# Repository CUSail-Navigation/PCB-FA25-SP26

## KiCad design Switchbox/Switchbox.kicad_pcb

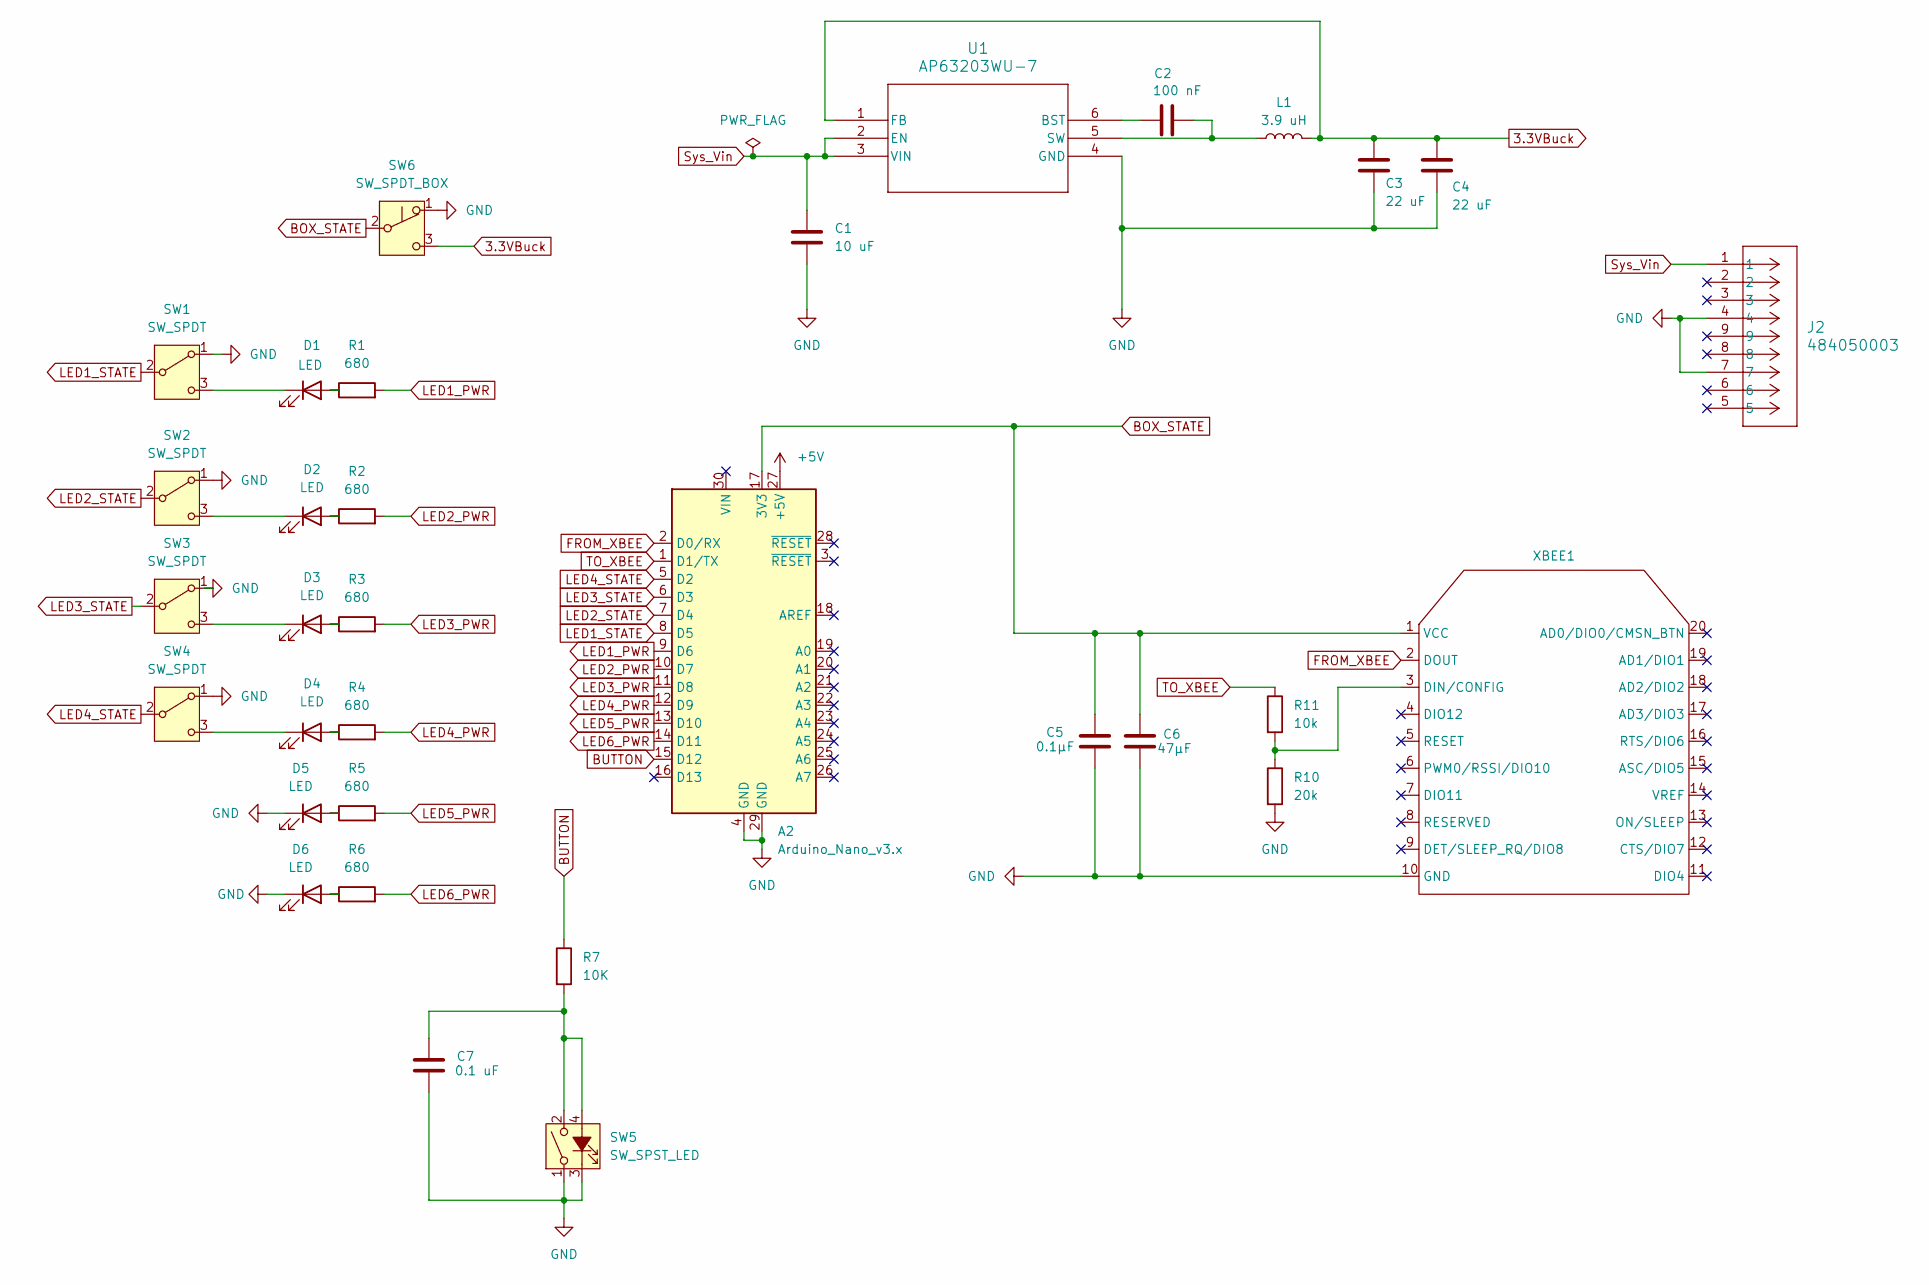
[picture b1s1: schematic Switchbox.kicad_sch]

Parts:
A2: Arduino_Nano_v3.x; Arduino_Nano
C1: 10 uF; CAPC1005X70N
C2: 100 nF; C_0603_1608Metric_Pad1.08x0.95mm_HandSolder
C3, C4: 22 uF; CAPC3216X190N
C5: 0.1µF; CAPC0603X33N
C6: 47µF; CAPC2012X145N
C7: 0.1 uF; CAPC0603X33N
D1, D2, D3, D4, D5, D6: LED; 2_pin_header
J2: 484050003; usba_footprint
L1: 3.9 uH; IND_BOURNS_SRR5018
R1, R2, R3, R4, R5, R6: 680; R_0805_2012Metric_Pad1.20x1.40mm_HandSolder
R7: 10K; R_0805_2012Metric_Pad1.20x1.40mm_HandSolder
R10: 20k; R_0805_2012Metric_Pad1.20x1.40mm_HandSolder
R11: 10k; R_0805_2012Metric_Pad1.20x1.40mm_HandSolder
SW1, SW2, SW3, SW4: SW_SPDT; 3_pin_header
SW5: SW_SPST_LED; 4_pin_header
SW6: SW_SPDT_BOX; 3_pin_header
U1: AP63203WU-7; buck
XBEE1: xbee

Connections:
3.3VBuck: C3.1, C4.1, L1.2, SW6.3 (C), U1.1 (FB)
+5V: A2.27 (+5V)
BOX_STATE: A2.17 (3V3), C5.1, C6.1, SW6.2 (B), XBEE1.1 (VCC)
BUTTON: A2.15 (D12), R7.1
FROM_XBEE: A2.2 (D0/RX), XBEE1.2 (DOUT)
GND: A2.4 (GND), A2.29 (GND), C1.2, C3.2, C4.2, C5.2, C6.2, C7.2, D5.1 (K), D6.1 (K), J2.4, J2.7, R10.2, SW1.1 (A), SW2.1 (A), SW3.1 (A), SW4.1 (A), SW5.1, SW5.3 (K), SW6.1 (A), U1.4 (GND), XBEE1.10 (GND)
LED1_PWR: A2.9 (D6), R1.2
LED1_STATE: A2.8 (D5), SW1.2 (B)
LED2_PWR: A2.10 (D7), R2.2
LED2_STATE: A2.7 (D4), SW2.2 (B)
LED3_PWR: A2.11 (D8), R3.2
LED3_STATE: A2.6 (D3), SW3.2 (B)
LED4_PWR: A2.12 (D9), R4.2
LED4_STATE: A2.5 (D2), SW4.2 (B)
LED5_PWR: A2.13 (D10), R5.2
LED6_PWR: A2.14 (D11), R6.2
unnamed: D1.2 (A), R1.1
unnamed: D1.1 (K), SW1.3 (C)
unnamed: D2.2 (A), R2.1
unnamed: D2.1 (K), SW2.3 (C)
unnamed: D3.2 (A), R3.1
unnamed: D3.1 (K), SW3.3 (C)
unnamed: D4.2 (A), R4.1
unnamed: D4.1 (K), SW4.3 (C)
unnamed: D5.2 (A), R5.1
unnamed: D6.2 (A), R6.1
unnamed: C7.1, R7.2, SW5.2, SW5.4 (A)
unnamed: C2.1, U1.6 (BST)
unnamed: C2.2, L1.1, U1.5 (SW)
unnamed: R10.1, R11.2, XBEE1.3 (DIN/CONFIG)
Sys_Vin: C1.1, J2.1, U1.2 (EN), U1.3 (VIN)
TO_XBEE: A2.1 (D1/TX), R11.1

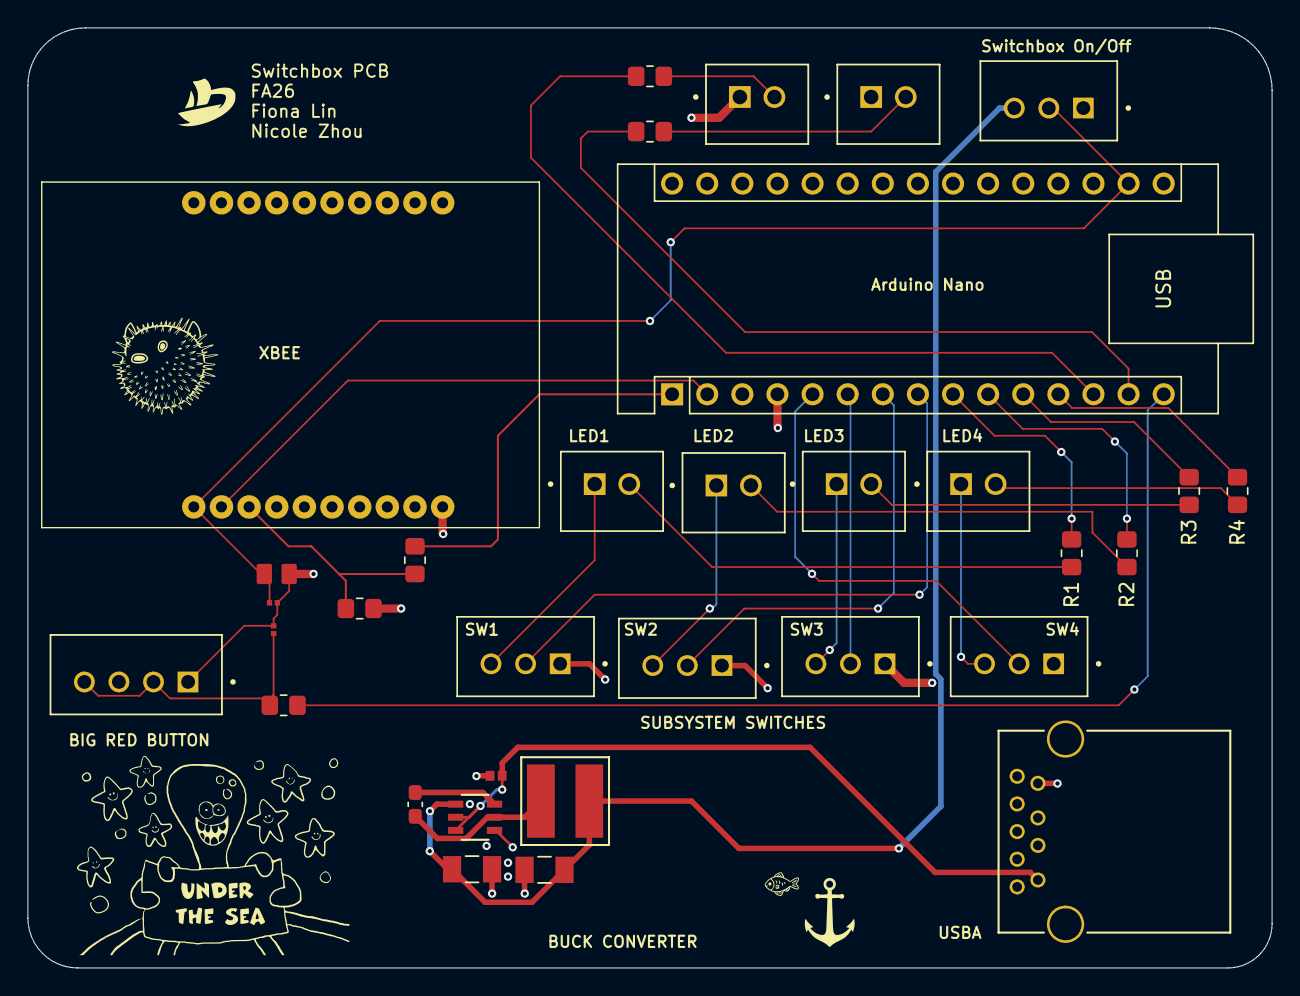
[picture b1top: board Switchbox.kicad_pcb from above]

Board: 4 copper layers, 90.0 x 68.0 mm, 33 parts (0 on the bottom side), 31 nets.

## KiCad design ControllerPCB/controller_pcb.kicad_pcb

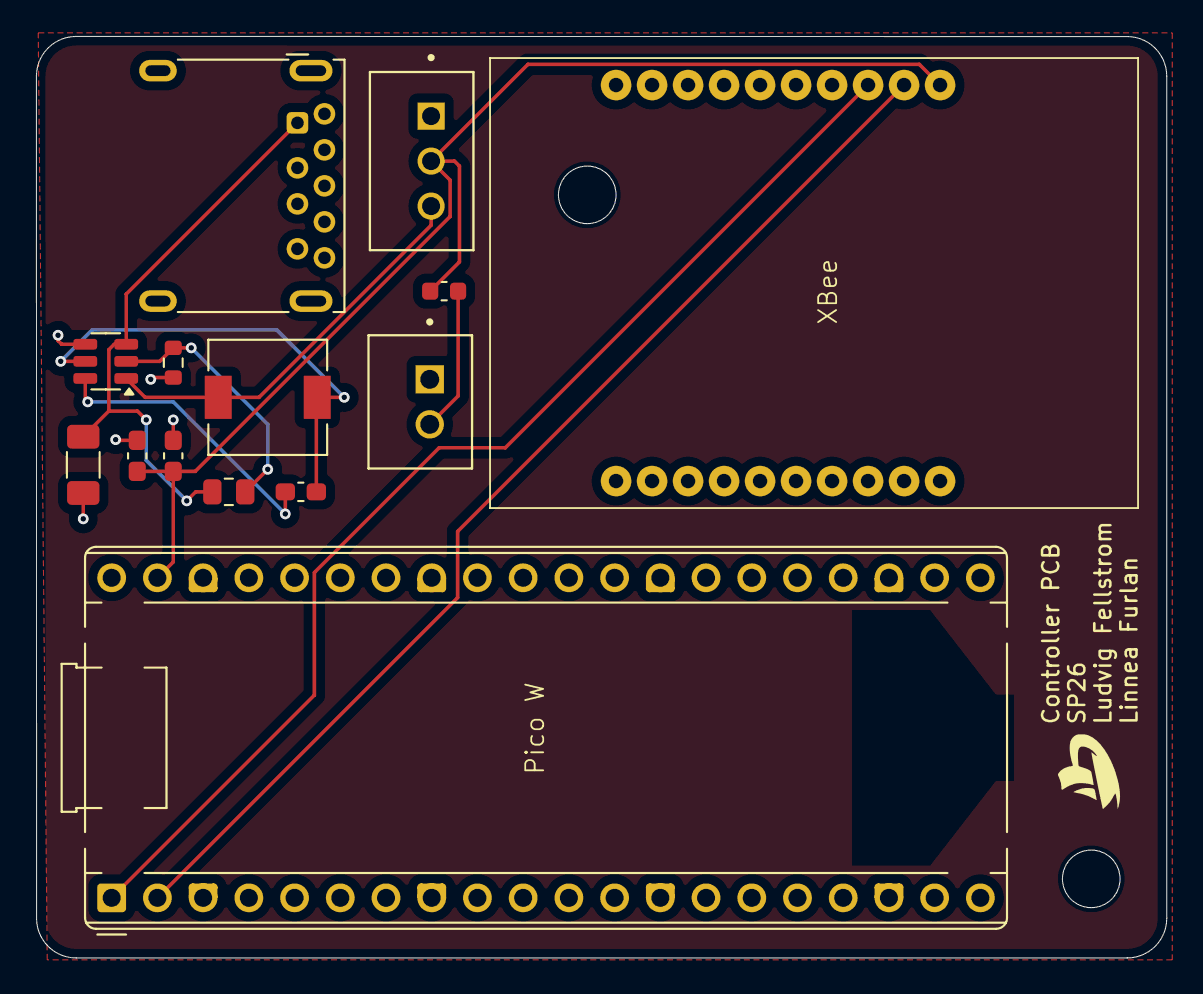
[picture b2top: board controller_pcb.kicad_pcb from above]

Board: 2 copper layers, 62.8 x 51.2 mm, 16 parts (0 on the bottom side), 10 nets.

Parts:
C1: 10µF; C_1206_3216Metric_Pad1.33x1.80mm_HandSolder
C2: 0.1µF; C_0603_1608Metric_Pad1.08x0.95mm_HandSolder
C3, C4: 22µF; C_0603_1608Metric_Pad1.08x0.95mm_HandSolder
D1: LED; 2_pin_header
H1, H2: MountingHole; MountingHole_3.2mm_M3
J1: USB3_A; USB3_A_Molex_48393-001
L1: 4.7µH; L_6.3x6.3_H3
PWR_SW1: SW_SPDT_BOX; 3_pin_header
R1: 100; C_0603_1608Metric
R3: 100k; R_0805_2012Metric
R_Buck_3: 100k; R_0603_1608Metric
U1: Pico; RaspberryPi_Pico_Common_THT
U2: xbee
U3: AP63203WU; TSOT-23-6

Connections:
/DOUT: U1.2 (GPIO1), U2.2 (DOUT)
GND: C1.2, C3.2, C4.2, D1.1 (K), J1.4 (GND), J1.7 (DRAIN), J1.10 (SHIELD), PWR_SW1.1 (A), R_Buck_3.2, U1.3 (GND), U1.8 (GND), U1.13 (GND), U1.18 (GND), U1.23 (GND), U1.28 (GND), U1.38 (GND), U2.10 (GND), U3.4 (GND)
unnamed: D1.2 (A), R1.2
unnamed: C1.1, J1.1 (VBUS), R3.2, U3.3 (IN)
unnamed: C3.1, C4.1, PWR_SW1.2 (B), R1.1, U1.39 (VSYS), U2.1 (VCC)
unnamed: L1.2, PWR_SW1.3 (C), U3.1 (FB)
unnamed: U1.1 (GPIO0), U2.3 (DIN/CONFIG)
unnamed: C2.1, U3.6 (BST)
unnamed: R3.1, R_Buck_3.1, U3.2 (EN)
unnamed: C2.2, L1.1, U3.5 (SW)

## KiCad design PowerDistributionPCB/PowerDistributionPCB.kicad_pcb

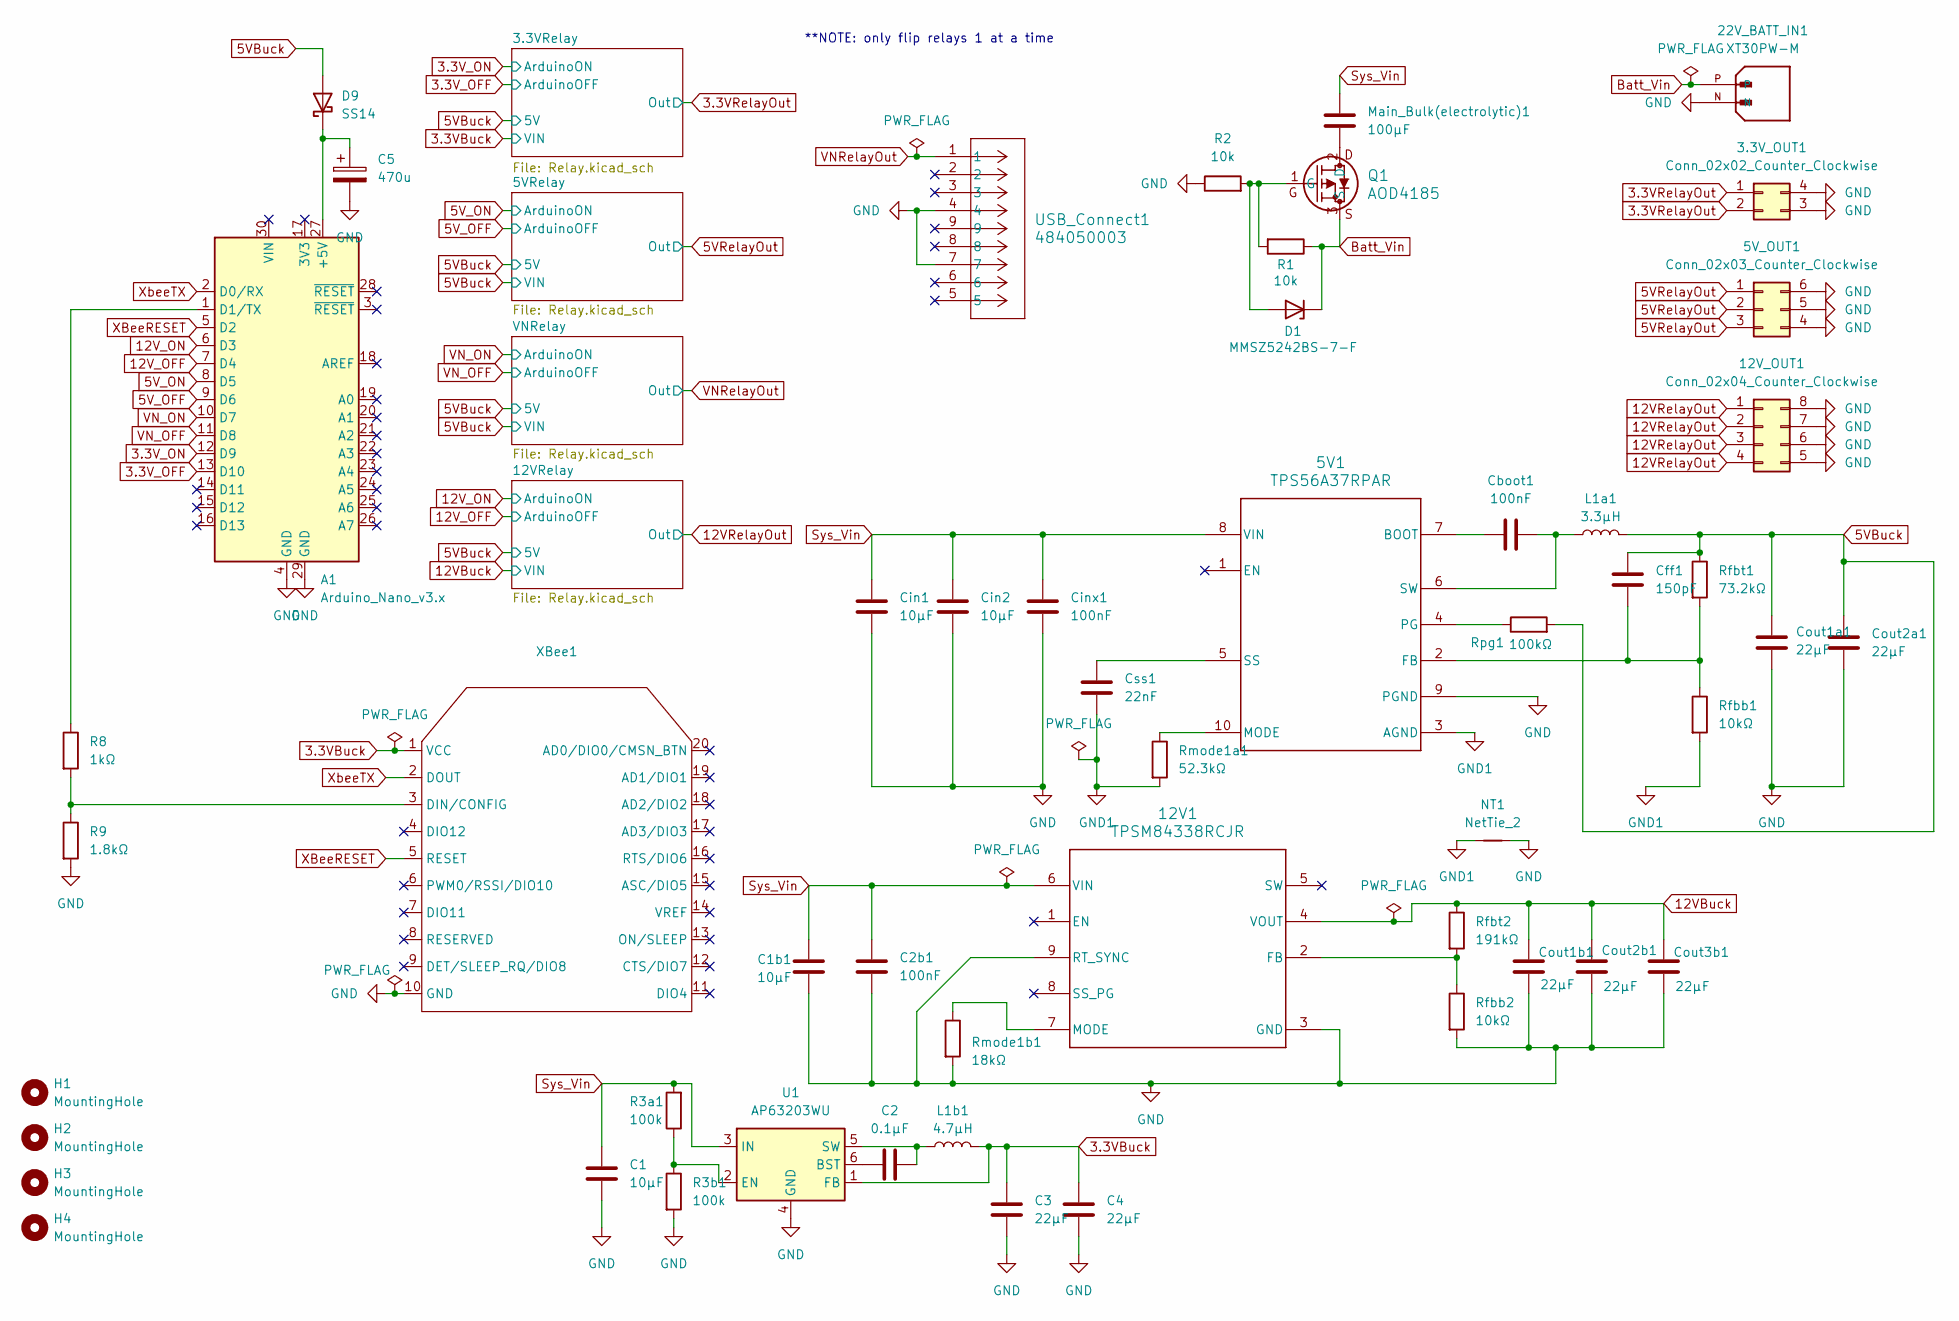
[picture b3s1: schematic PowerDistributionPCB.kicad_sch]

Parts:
3.3V_OUT1: Conn_02x02_Counter_Clockwise; Molex_Mini-Fit_Jr_5566-04A_2x02_P4.20mm_Vertical
5V1: TPS56A37RPAR; RPA0010A-MFG
5V_OUT1: Conn_02x03_Counter_Clockwise; Molex_Mini-Fit_Jr_5566-06A_2x03_P4.20mm_Vertical
12V1: TPSM84338RCJR; buck_correct
12V_OUT1: Conn_02x04_Counter_Clockwise; Molex_Mini-Fit_Jr_5566-08A_2x04_P4.20mm_Vertical
22V_BATT_IN1: XT30PW-M; PARTREV 1.2
A1: Arduino_Nano_v3.x; Arduino_Nano
C1: 10µF; C_1206_3216Metric_Pad1.33x1.80mm_HandSolder
C1b1: 10µF; C_1210_3225Metric_Pad1.33x2.70mm_HandSolder
C2: 0.1µF; C_0603_1608Metric_Pad1.08x0.95mm_HandSolder
C2b1: 100nF; C_0201_0603Metric_Pad0.64x0.40mm_HandSolder
C3, C4: 22µF; C_0603_1608Metric_Pad1.08x0.95mm_HandSolder
C5: 470u; CP_Elec_8x10.5
Cboot1: 100nF; C_0201_0603Metric_Pad0.64x0.40mm_HandSolder
Cff1: 150pF; C_0201_0603Metric_Pad0.64x0.40mm_HandSolder
Cin1, Cin2: 10µF; C_1210_3225Metric_Pad1.33x2.70mm_HandSolder
Cinx1: 100nF; C_0805_2012Metric_Pad1.18x1.45mm_HandSolder
Cout1a1, Cout2a1: 22µF; C_1210_3225Metric_Pad1.33x2.70mm_HandSolder
Cout1b1, Cout2b1, Cout3b1: 22µF; C_1206_3216Metric_Pad1.33x1.80mm_HandSolder
Css1: 22nF; C_0402_1005Metric_Pad0.74x0.62mm_HandSolder
D1: MMSZ5242BS-7-F
D9: SS14; D_SMA
H1, H2, H3, H4: MountingHole; MountingHole_3.2mm_M3
L1a1: 3.3µH; L_Coilcraft_XAL7070-XXX
L1b1: 4.7µH; VLS4012
Main_Bulk(electrolytic)1: 100µF; C_1210_3225Metric_Pad1.33x2.70mm_HandSolder
NT1: NetTie_2; NetTie-2_SMD_Pad0.5mm
Q1: AOD4185
R1, R2: 10k; R_0805_2012Metric_Pad1.20x1.40mm_HandSolder
R3a1, R3b1: 100k; R_0805_2012Metric_Pad1.20x1.40mm_HandSolder
R8: 1kΩ; R_0805_2012Metric_Pad1.20x1.40mm_HandSolder
R9: 1.8kΩ; R_0805_2012Metric_Pad1.20x1.40mm_HandSolder
Rfbb1, Rfbb2: 10kΩ; R_0201_0603Metric_Pad0.64x0.40mm_HandSolder
Rfbt1: 73.2kΩ; R_0805_2012Metric_Pad1.20x1.40mm_HandSolder
Rfbt2: 191kΩ; R_0201_0603Metric_Pad0.64x0.40mm_HandSolder
Rmode1a1: 52.3kΩ; R_0402_1005Metric_Pad0.72x0.64mm_HandSolder
Rmode1b1: 18kΩ; C_0201_0603Metric_Pad0.64x0.40mm_HandSolder
Rpg1: 100kΩ; R_0402_1005Metric_Pad0.72x0.64mm_HandSolder
U1: AP63203WU; TSOT-23-6
USB_Connect1: 484050003; CONN_484050003_MOL
XBee1: XBee

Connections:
3.3VRelayOut: 3.3V_OUT1.1, 3.3V_OUT1.2; also elsewhere on the board
3.3V_OFF: A1.13 (D10); also elsewhere on the board
3.3V_ON: A1.12 (D9); also elsewhere on the board
5VBuck: Cff1.1, Cout1a1.1, Cout2a1.1, D9.2 (A), L1a1.2, Rfbt1.1, Rpg1.2; also elsewhere on the board
5VRelayOut: 5V_OUT1.1, 5V_OUT1.2, 5V_OUT1.3; also elsewhere on the board
5V_OFF: A1.9 (D6); also elsewhere on the board
5V_ON: A1.8 (D5); also elsewhere on the board
12VBuck: 12V1.4 (VOUT), Cout1b1.1, Cout2b1.1, Cout3b1.1, Rfbt2.1; also elsewhere on the board
12VRelayOut: 12V_OUT1.1, 12V_OUT1.2, 12V_OUT1.3, 12V_OUT1.4; also elsewhere on the board
12V_OFF: A1.7 (D4); also elsewhere on the board
12V_ON: A1.6 (D3); also elsewhere on the board
Batt_Vin: 22V_BATT_IN1.P, D1.1 (K), Q1.3 (S), R1.1; also elsewhere on the board
GND: 3.3V_OUT1.3, 3.3V_OUT1.4, 5V1.9 (PGND), 5V_OUT1.4, 5V_OUT1.5, 5V_OUT1.6, 12V1.3 (GND), 12V1.9 (RT_SYNC), 12V_OUT1.5, 12V_OUT1.6, 12V_OUT1.7, 12V_OUT1.8, 22V_BATT_IN1.N, A1.4 (GND), A1.29 (GND), C1.2, C1b1.2, C2b1.2, C3.2, C4.2, C5.2, Cin1.2, Cin2.2, Cinx1.2, Cout1a1.2, Cout1b1.2, Cout2a1.2, Cout2b1.2, Cout3b1.2, NT1.2, R2.1, R3b1.2, R9.2, Rfbb2.2, Rmode1b1.2, U1.4 (GND), USB_Connect1.4, USB_Connect1.7, XBee1.10 (GND); also elsewhere on the board
GND1: 5V1.3 (AGND), Css1.2, NT1.1, Rfbb1.2, Rmode1a1.2
unnamed: 5V1.7 (BOOT), Cboot1.2
unnamed: 5V1.2 (FB), Cff1.2, Rfbb1.1, Rfbt1.2
unnamed: 5V1.10 (MODE), Rmode1a1.1
unnamed: 5V1.4 (PG), Rpg1.1
unnamed: 5V1.5 (SS), Css1.1
unnamed: 5V1.6 (SW), Cboot1.1, L1a1.1
unnamed 20: 12V1.2 (FB), Rfbb2.1, Rfbt2.2; also elsewhere on the board
unnamed 21: 12V1.7 (MODE), Rmode1b1.1; also elsewhere on the board
unnamed: A1.27 (+5V), C5.1, D9.1 (K)
unnamed: A1.1 (D1/TX), R8.1
unnamed: D1.2 (A), Q1.1 (G), R1.2, R2.2
unnamed 37: Main_Bulk(electrolytic)1.2, Q1.2 (D); also elsewhere on the board
unnamed: C2.1, U1.6 (BST)
unnamed: R3a1.1, R3b1.1, U1.2 (EN)
unnamed: C2.2, L1b1.1, U1.5 (SW)
unnamed: R8.2, R9.1, XBee1.3 (DIN/CONFIG)
Sys_Vin: 5V1.8 (VIN), 12V1.6 (VIN), C1.1, C1b1.1, C2b1.1, Cin1.1, Cin2.1, Cinx1.1, Main_Bulk(electrolytic)1.1, R3a1.2, U1.3 (IN); also elsewhere on the board
VNRelayOut: USB_Connect1.1; also elsewhere on the board
VN_OFF: A1.11 (D8); also elsewhere on the board
VN_ON: A1.10 (D7); also elsewhere on the board
XBeeRESET: A1.5 (D2), XBee1.5 (RESET)
XbeeTX: A1.2 (D0/RX), XBee1.2 (DOUT)

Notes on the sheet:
**NOTE: only flip relays 1 at a time

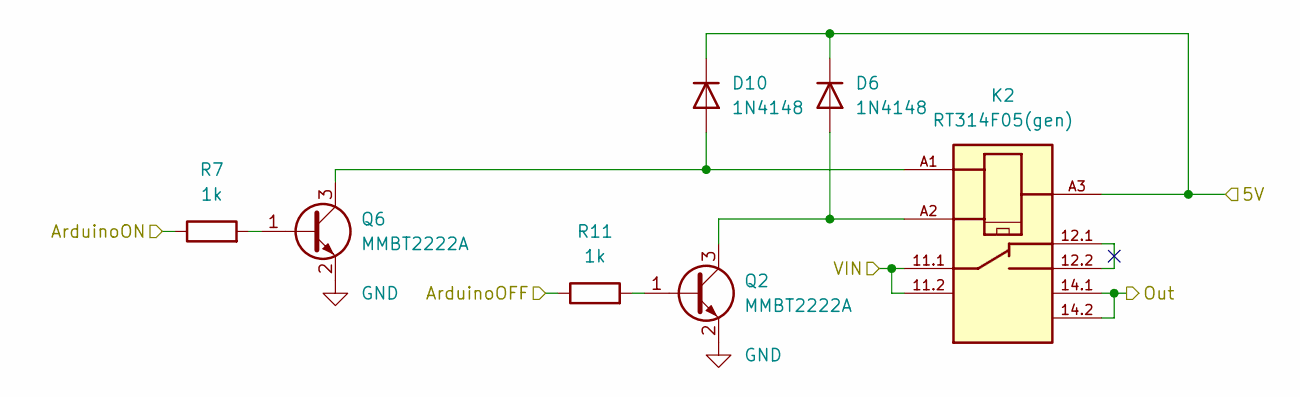
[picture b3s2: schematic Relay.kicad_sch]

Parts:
D6, D10: 1N4148; D_DO-35_SOD27_P7.62mm_Horizontal
K2: RT314F05(gen); RT314F05; VOLTAGE_RATING 5VDC; PART_DESCRIPTION RELAY GEN PURPOSE SPDT 16A 5V
Q2, Q6: MMBT2222A; SOT-23
R7, R11: 1k; R_0805_2012Metric_Pad1.20x1.40mm_HandSolder

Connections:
3.3VRelayOut: K2.14.1, K2.14.2; also elsewhere on the board
3.3V_OFF: R11.1; also elsewhere on the board
3.3V_ON: R7.1; also elsewhere on the board
5VBuck: D6.1 (K), D10.1 (K), K2.A3; also elsewhere on the board
GND: Q2.2 (E), Q6.2 (E); also elsewhere on the board
unnamed: D6.2 (A), K2.A2, Q2.3 (C)
unnamed: D10.2 (A), K2.A1, Q6.3 (C)
unnamed: K2.11.1, K2.11.2
unnamed: Q2.1 (B), R11.2
unnamed: Q6.1 (B), R7.2

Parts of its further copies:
D2, D3, D4, D5, D7, D8: 1N4148; D_DO-35_SOD27_P7.62mm_Horizontal
K1, K3, K4: RT314F05(gen); RT314F05; VOLTAGE_RATING 5VDC; PART_DESCRIPTION RELAY GEN PURPOSE SPDT 16A 5V
Q7, Q8, Q9, Q10, Q11, Q12: MMBT2222A; SOT-23
R3, R4, R5, R6, R15, R16: 1k; R_0805_2012Metric_Pad1.20x1.40mm_HandSolder

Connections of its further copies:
5VBuck: D2.1 (K), D3.1 (K), D4.1 (K), D5.1 (K), D7.1 (K), D8.1 (K), K1.12.1, K1.12.2, K1.A3, K3.12.1, K3.12.2, K3.A3, K4.A3; also elsewhere on the board
5VRelayOut: K1.14.1, K1.14.2; also elsewhere on the board
5V_OFF: R4.1; also elsewhere on the board
5V_ON: R3.1; also elsewhere on the board
12VBuck: K4.12.1, K4.12.2; also elsewhere on the board
12VRelayOut: K4.14.1, K4.14.2; also elsewhere on the board
12V_OFF: R16.1; also elsewhere on the board
12V_ON: R15.1; also elsewhere on the board
GND: Q7.2 (E), Q8.2 (E), Q9.2 (E), Q10.2 (E), Q11.2 (E), Q12.2 (E); also elsewhere on the board
unnamed: D2.2 (A), K1.A1, Q10.3 (C)
unnamed: D3.2 (A), K1.A2, Q11.3 (C)
unnamed: D4.2 (A), K3.A1, Q7.3 (C)
unnamed: D5.2 (A), K3.A2, Q8.3 (C)
unnamed: D7.2 (A), K4.A1, Q9.3 (C)
unnamed: D8.2 (A), K4.A2, Q12.3 (C)
unnamed: K1.11.1, K1.11.2
unnamed: K3.11.1, K3.11.2
unnamed: K4.11.1, K4.11.2
unnamed: Q7.1 (B), R5.2
unnamed: Q8.1 (B), R6.2
unnamed: Q9.1 (B), R15.2
unnamed: Q10.1 (B), R3.2
unnamed: Q11.1 (B), R4.2
unnamed: Q12.1 (B), R16.2
VNRelayOut: K3.14.1, K3.14.2; also elsewhere on the board
VN_OFF: R6.1; also elsewhere on the board
VN_ON: R5.1; also elsewhere on the board

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
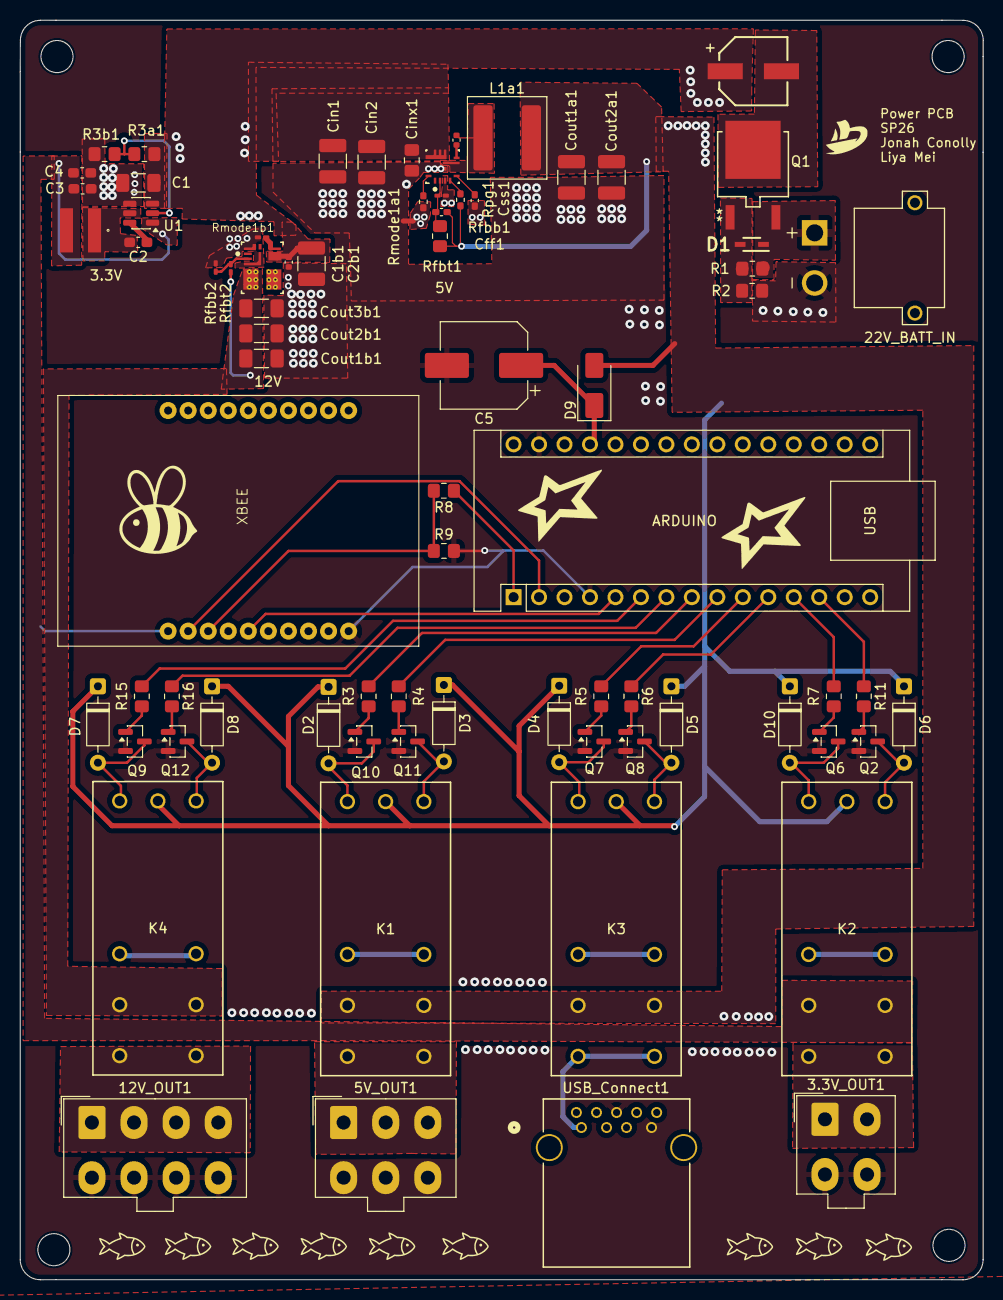
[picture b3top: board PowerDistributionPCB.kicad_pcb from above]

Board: 4 copper layers, 96.0 x 125.6 mm, 80 parts (0 on the bottom side), 57 nets.

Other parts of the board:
12V: TPSM84338RCJR; buck_correct
22V_BATT_IN: XT30PW-M
Main_Bulk: 100µF; WCAP-PSLP_6.3X7.7_DXL_

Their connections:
12VBuck: 12V.4 (VOUT); also elsewhere on the board
Batt_Vin: 22V_BATT_IN.P; also elsewhere on the board
GND: 12V.3 (GND), 12V.9 (RT_SYNC), 22V_BATT_IN.N; also elsewhere on the board
unnamed 20: 12V.2 (FB); also elsewhere on the board
unnamed 21: 12V.7 (MODE); also elsewhere on the board
unnamed 37: Main_Bulk.2; also elsewhere on the board
Sys_Vin: 12V.6 (VIN), Main_Bulk.1; also elsewhere on the board

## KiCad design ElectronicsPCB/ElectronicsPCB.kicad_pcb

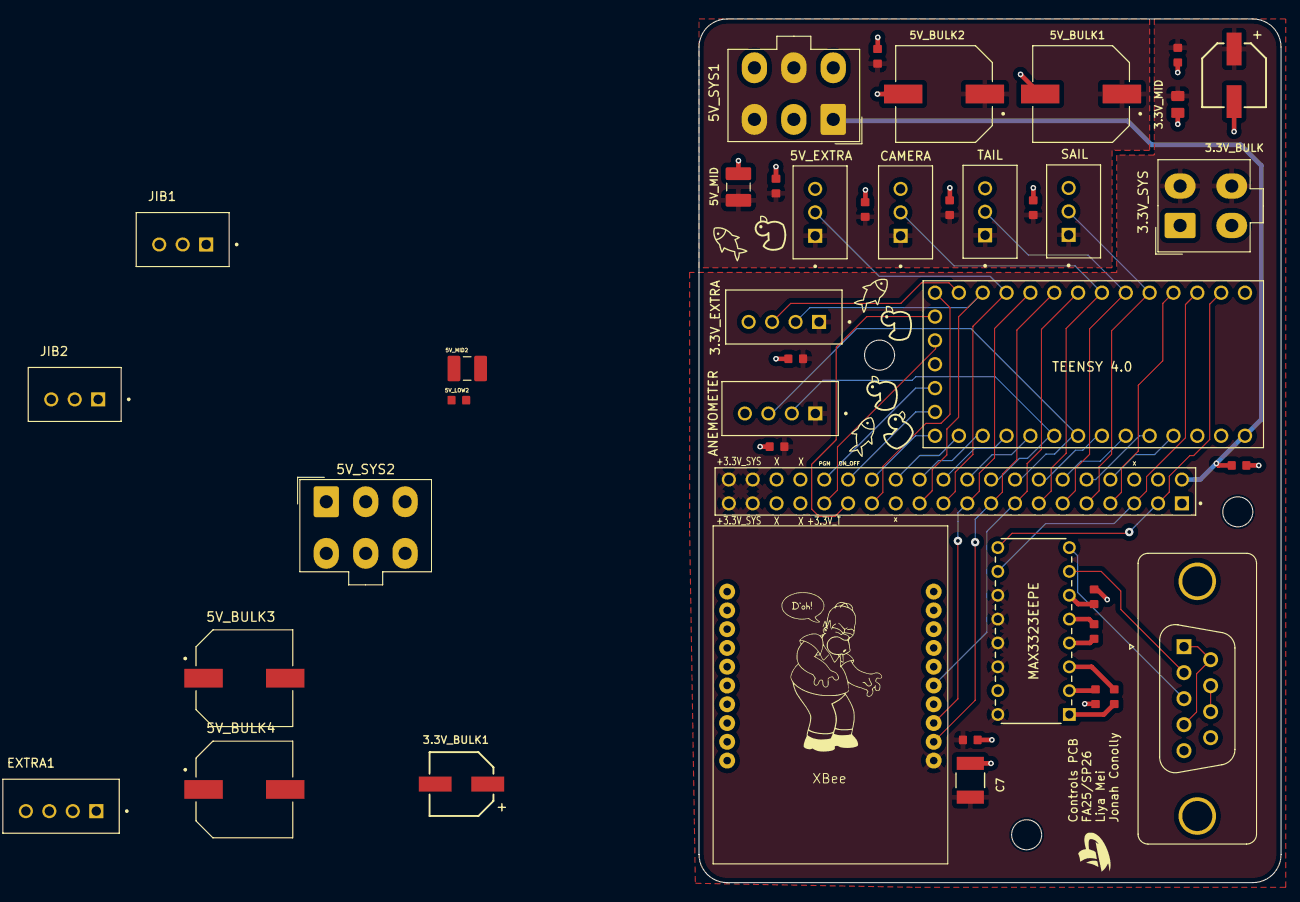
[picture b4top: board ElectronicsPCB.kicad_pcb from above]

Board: 2 copper layers, 62.0 x 92.0 mm, 45 parts (0 on the bottom side), 45 nets.

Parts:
3.3V_BULK, 3.3V_BULK1: 220uf; CAP_87510_220uf
3.3V_EXTRA: B4B-XH-A
3.3V_LOW1, 5V_LOW1, 5V_LOW2: 0.1uf; CAP_CL10B_01uf_0603
3.3V_MID1: 10uf; CAP_CL21A_10uf_0805
3.3V_SYS: Conn_02x02_Counter_Clockwise; Molex_Mini-Fit_Jr_5566-04A_2x02_P4.20mm_Vertical
5V_BULK1, 5V_BULK2, 5V_BULK3, 5V_BULK4: 1000uf; CAP_EEE1A_1000uf
5V_EXTRA: B3B-XH-A
5V_MID1, 5V_MID2: 22uf; CAP_CL32A_22uf_1210
5V_SYS1, 5V_SYS2: Conn_02x03_Counter_Clockwise; Molex_Mini-Fit_Jr_5566-06A_2x03_P4.20mm_Vertical
ANEMOMETER: B4B-XH-A
C1, C2, C3, C4, C5, C6, C8, C9, C10, C11, C12: 0.1µF; CAP_CL10B_01uf_0603
C7: 47µF; CAP_C3225_47uf_1210
CAMERA: B3B-XH-A
EXTRA1: B4B-XH-A
H1, H2, H3: MountingHole; MountingHole_3.2mm_M3
HEADERS1: M20-7832046; HARWIN_M20-7832046
JIB1, JIB2: B3B-XH-A
MAX3323EEPE: max3323eepe+; MAX3323EEPE+
SAIL: B3B-XH-A
TAIL: B3B-XH-A
TEENSY 4.0: DEV-15583; MODULE_DEV-15583
TeensyC0.1: 0.1µF; CAP_CL10B_01uf_0603
VectorNavInput1: DE9_Socket_MountingHoles; DSUB-9_Socket_Vertical_P2.77x2.84mm_MountingHoles
XBEE1: XBee

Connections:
2: HEADERS1.7, TEENSY 4.0.2
12: HEADERS1.27, TEENSY 4.0.12
13: HEADERS1.28, TEENSY 4.0.13
14: HEADERS1.26, TEENSY 4.0.14
15: HEADERS1.24, TEENSY 4.0.15
16: HEADERS1.22, TEENSY 4.0.16
17: HEADERS1.20, TEENSY 4.0.17
20: HEADERS1.14, TEENSY 4.0.20
21: HEADERS1.12, TEENSY 4.0.21
22: HEADERS1.10, TEENSY 4.0.22
23: HEADERS1.8, TEENSY 4.0.23
+3.3V_SYS: 3.3V_BULK.1, 3.3V_BULK1.1, 3.3V_EXTRA.1, 3.3V_LOW1.1, 3.3V_MID1.1, 3.3V_SYS.2, 3.3V_SYS.4, ANEMOMETER.1, C5.1, C6.1, C7.1, C8.1, EXTRA1.1, HEADERS1.37, HEADERS1.38, HEADERS1.39, HEADERS1.40, MAX3323EEPE.11 (TXENABLE), MAX3323EEPE.12 (RENABLE), MAX3323EEPE.13 (VL), MAX3323EEPE.14 (*SHDN), MAX3323EEPE.16 (VCC), XBEE1.1 (VCC)
+5V_SYS: 5V_EXTRA.1, 5V_SYS1.1, 5V_SYS1.3, 5V_SYS1.5, CAMERA.1, SAIL.1, TAIL.1, TEENSY 4.0.VIN
+5V_SYS1: 5V_BULK1.1, 5V_BULK2.1, 5V_LOW1.2, 5V_MID1.2, C10.1, C12.1, HEADERS1.2, JIB1.1, TeensyC0.1.2
+5V_SYS2: 5V_BULK3.1, 5V_BULK4.1, 5V_LOW2.2, 5V_MID2.2, 5V_SYS2.1, 5V_SYS2.3, 5V_SYS2.5, C9.1, C11.1, JIB2.1
Camera: CAMERA.2, HEADERS1.13, TEENSY 4.0.5
Extra3: 5V_EXTRA.2, TEENSY 4.0.9
Extra40: 3.3V_EXTRA.2, EXTRA1.2, TEENSY 4.0.10
Extra41: 3.3V_EXTRA.3, EXTRA1.3, TEENSY 4.0.11
GND: 3.3V_BULK.2, 3.3V_BULK1.2, 3.3V_EXTRA.4, 3.3V_LOW1.2, 3.3V_MID1.2, 3.3V_SYS.1, 3.3V_SYS.3, 5V_BULK1.2, 5V_BULK2.2, 5V_BULK3.2, 5V_BULK4.2, 5V_EXTRA.3, 5V_LOW1.1, 5V_LOW2.1, 5V_MID1.1, 5V_MID2.1, 5V_SYS1.2, 5V_SYS1.4, 5V_SYS1.6, 5V_SYS2.2, 5V_SYS2.4, 5V_SYS2.6, ANEMOMETER.4, C1.2, C4.1, C5.2, C6.2, C7.2, C8.2, C9.2, C10.2, C11.2, C12.2, CAMERA.3, EXTRA1.4, HEADERS1.1, HEADERS1.4, JIB1.3, JIB2.3, MAX3323EEPE.15 (GND), SAIL.3, TAIL.3, TEENSY 4.0.G3, TeensyC0.1.1, VectorNavInput1.5, XBEE1.10 (GND)
JIB1: HEADERS1.21, JIB1.2
JIB2: HEADERS1.23, JIB2.2
unnamed: C3.1, MAX3323EEPE.1 (C1+)
unnamed: C3.2, MAX3323EEPE.3 (C1-)
unnamed: C2.1, MAX3323EEPE.4 (C2+)
unnamed: C2.2, MAX3323EEPE.5 (C2-)
unnamed: C4.2, MAX3323EEPE.2 (V+)
unnamed: C1.1, MAX3323EEPE.6 (V-)
unnamed: VectorNavInput1.1, VectorNavInput1.4, VectorNavInput1.6
unnamed: VectorNavInput1.7, VectorNavInput1.8
ON_OFF: HEADERS1.30, TEENSY 4.0.ON-OFF (ON/OFF)
PGM: HEADERS1.32, TEENSY 4.0.PGM (PROGRAM)
Sail: HEADERS1.9, SAIL.2, TEENSY 4.0.3
TEENSY_3.3V: HEADERS1.31, TEENSY 4.0.3.3V_1
Tail: HEADERS1.11, TAIL.2, TEENSY 4.0.4
TeensyRX: HEADERS1.3, MAX3323EEPE.9 (ROUT1), TEENSY 4.0.0
TeensyTX: HEADERS1.5, MAX3323EEPE.10 (TIN1), TEENSY 4.0.1
VBAT: HEADERS1.29, TEENSY 4.0.VBAT
VectorNavRX: MAX3323EEPE.7 (TOUT1), VectorNavInput1.2
VectorNavTX: MAX3323EEPE.8 (RIN1), VectorNavInput1.3
WindData0: ANEMOMETER.2, HEADERS1.18, TEENSY 4.0.18
WindData1: ANEMOMETER.3, HEADERS1.16, TEENSY 4.0.19
XBeeRESET: HEADERS1.15, TEENSY 4.0.6, XBEE1.5 (RESET)
XBeeRX: HEADERS1.19, TEENSY 4.0.8, XBEE1.3 (DIN/CONFIG)
XBeeTX: HEADERS1.17, TEENSY 4.0.7, XBEE1.2 (DOUT)

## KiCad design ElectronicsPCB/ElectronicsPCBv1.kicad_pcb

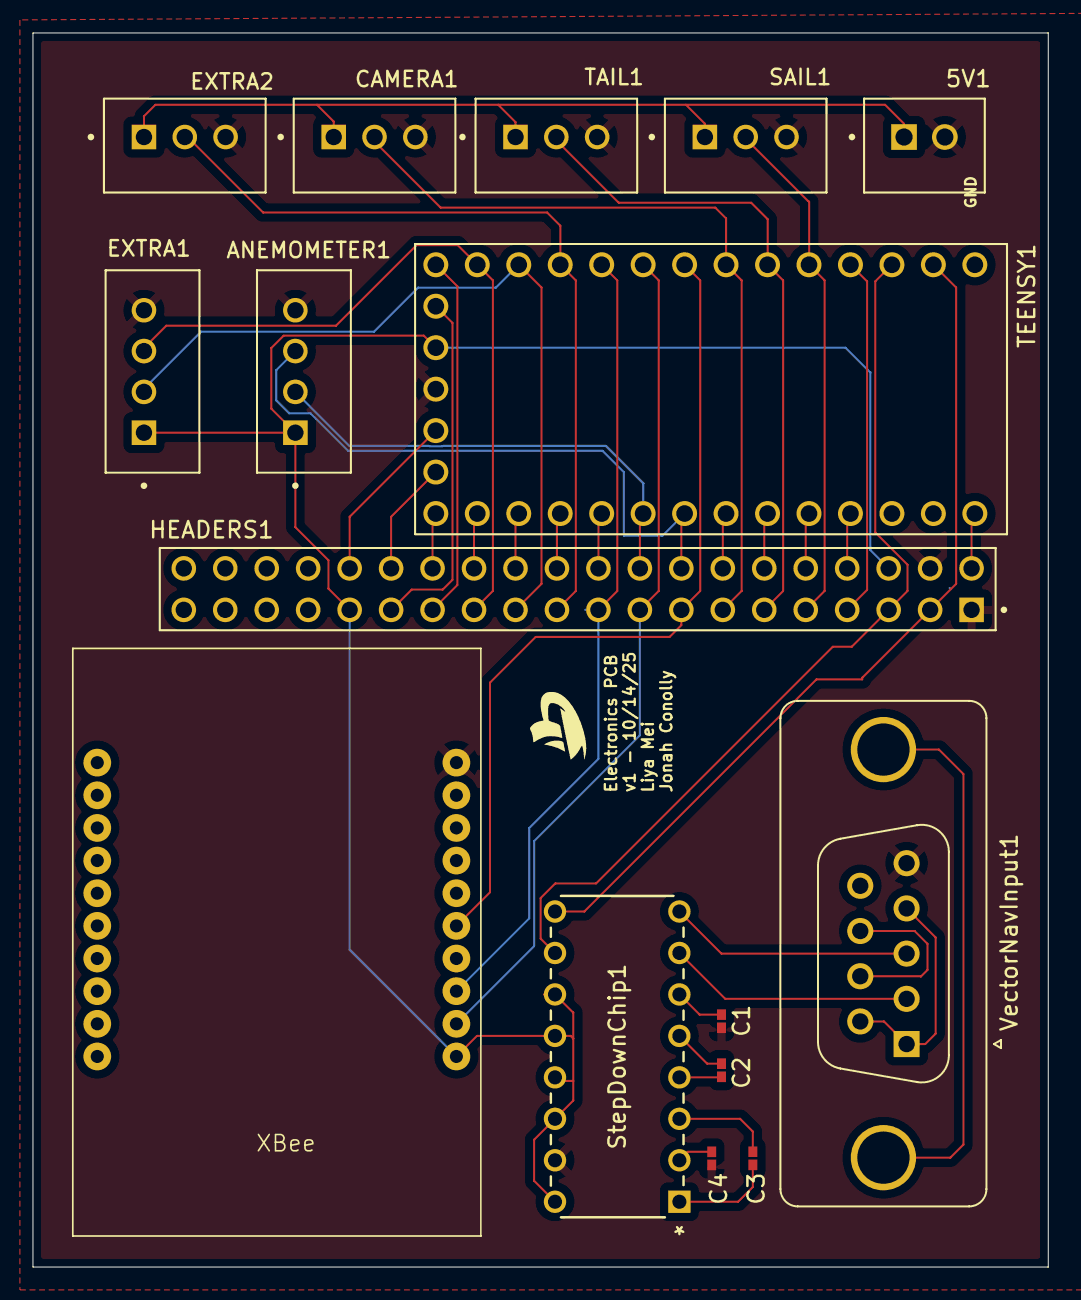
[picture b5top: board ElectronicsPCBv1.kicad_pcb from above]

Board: 4 copper layers, 62.2 x 75.6 mm, 16 parts (0 on the bottom side), 41 nets.

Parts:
5V1: B2B-XH-A
ANEMOMETER1: B4B-XH-A
C1, C2, C3, C4: 0.1µF; C0402C104K4RACTU_0.1µF
CAMERA1: B3B-XH-A
EXTRA1: B4B-XH-A
EXTRA2: B3B-XH-A
HEADERS1: M20-7832046; HARWIN_M20-7832046
SAIL1: B3B-XH-A
StepDownChip1: max3323eepe+; MAX3323EEPE+
TAIL1: B3B-XH-A
TEENSY1: DEV-15583; MODULE_DEV-15583
VectorNavInput1: DE9_Socket_MountingHoles; DSUB-9_Socket_Vertical_P2.77x2.84mm_MountingHoles
XBEE1: XBee

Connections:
2: HEADERS1.7, TEENSY1.2
12: HEADERS1.27, TEENSY1.12
13: HEADERS1.28, TEENSY1.13
14: HEADERS1.26, TEENSY1.14
15: HEADERS1.24, TEENSY1.15
16: HEADERS1.22, TEENSY1.16
17: HEADERS1.20, TEENSY1.17
20: HEADERS1.14, TEENSY1.20
21: HEADERS1.12, TEENSY1.21
22: HEADERS1.10, TEENSY1.22
23: HEADERS1.8, TEENSY1.23
+3.3V: ANEMOMETER1.1, EXTRA1.1, HEADERS1.6, HEADERS1.31, StepDownChip1.11 (TXENABLE), StepDownChip1.12 (RENABLE), StepDownChip1.13 (VL), StepDownChip1.14 (*SHDN), StepDownChip1.16 (VCC), TEENSY1.3.3V_1, XBEE1.1 (VCC)
+5V: 5V1.1, CAMERA1.1, EXTRA2.1, SAIL1.1, TAIL1.1
Camera: CAMERA1.2, HEADERS1.13, TEENSY1.5
Extra3: EXTRA2.2, HEADERS1.21, TEENSY1.9
Extra40: EXTRA1.2, HEADERS1.23, TEENSY1.10
Extra41: EXTRA1.3, HEADERS1.25, TEENSY1.11
GND: 5V1.2, ANEMOMETER1.4, C1.2, C4.1, CAMERA1.3, EXTRA1.4, EXTRA2.3, HEADERS1.1, HEADERS1.4, SAIL1.3, StepDownChip1.15 (GND), TAIL1.3, TEENSY1.G2, VectorNavInput1.5, XBEE1.10 (GND)
unnamed: C3.1, StepDownChip1.1 (C1+)
unnamed: C3.2, StepDownChip1.3 (C1-)
unnamed: C2.1, StepDownChip1.4 (C2+)
unnamed: C2.2, StepDownChip1.5 (C2-)
unnamed: C4.2, StepDownChip1.2 (V+)
unnamed: C1.1, StepDownChip1.6 (V-)
unnamed: VectorNavInput1.1, VectorNavInput1.4, VectorNavInput1.6
unnamed: VectorNavInput1.7, VectorNavInput1.8
ON_OFF: HEADERS1.30, TEENSY1.ON-OFF (ON/OFF)
PGM: HEADERS1.32, TEENSY1.PGM (PROGRAM)
Sail: HEADERS1.9, SAIL1.2, TEENSY1.3
Tail: HEADERS1.11, TAIL1.2, TEENSY1.4
TeensyRX: HEADERS1.3, StepDownChip1.9 (ROUT1), TEENSY1.0
TeensyTX: HEADERS1.5, StepDownChip1.10 (TIN1), TEENSY1.1
TeensyVIN: HEADERS1.2, TEENSY1.VIN
VBAT: HEADERS1.29, TEENSY1.VBAT
VectorNavRX: StepDownChip1.7 (TOUT1), VectorNavInput1.2
VectorNavTX: StepDownChip1.8 (RIN1), VectorNavInput1.3
WindData0: ANEMOMETER1.2, HEADERS1.18, TEENSY1.18
WindData1: ANEMOMETER1.3, HEADERS1.16, TEENSY1.19
XBeeRESET: HEADERS1.15, TEENSY1.6, XBEE1.5 (RESET)
XBeeRX: HEADERS1.19, TEENSY1.8, XBEE1.3 (DIN/CONFIG)
XBeeTX: HEADERS1.17, TEENSY1.7, XBEE1.2 (DOUT)
